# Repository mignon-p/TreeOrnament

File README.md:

This repository contains the [KiCad][1] and [Gerber][2] files for a
PCB Christmas ornament shaped like a Christmas tree.

The little tree has candy canes on the silkscreen, ornaments made out
of exposed copper, and a trunk made out of exposed FR4.  The garland
is made out of resistors, and the lights are LEDs, powered by a micro
USB connector on the back.

You can hang the ornament on your tree by putting a string through the
hole at the top of the ornament.  Or, you can use it as a standalone
decoration, in which case the USB cable in the back acts as a sort of
"[kickstand](kickstand.jpg)" to hold the tree up.

This README should contain enough information to build the ornament.
However, if you want more detailed, step-by-step instructions with
pictures, I've also written
[an Instructable on how to build the ornament][17].

## Bill of Materials

* USB Micro B connector, qty 1.  Würth part number 614105150721.
  Digi-Key part number [732-5958-1-ND][3].

* 1/8 watt resistors, qty 14.  Make sure the length of the resistor is
  around 3.3-3.6 mm.  The minimum resistor value you should use is 150
  Ohms.  However, I found that to be too bright, so I eventually
  settled on 1k Ohm resistors.  Especially if you use different LEDs
  than I did, you should experiment to see what resistor value gives
  you a brightness that you like.  For 1k Ohm resistors: Stackpole
  part number CF18JT1K00.  Digi-Key part number [CF18JT1K00CT-ND][4].

* 3mm LEDs, qty 14.  Just about any 3mm LED should do, but I used
  color-changing LEDs to [add a bit of motion][13] to the ornament.
  When soldering the LEDs, make sure the short leg of the LED goes
  into the square pad, and the long leg of the LED goes into the round
  pad.  For color-changing LEDs: SparkFun part number [COM-11448][5].
  Digi-Key part number [1568-1196-ND][6].

* Optional: 3.3µF 0805 ceramic capacitor, qty 3.  These probably
  aren't essential, but since decoupling capacitors are considered to
  be a good idea, I added pads for three capacitors on the back of the
  board.  (Though if you're using ordinary LEDs, you really don't need
  them, since the current will be constant.  I only added them because
  I'm using color-change LEDs, which probably use PWM to fade through
  the colors.)  Unlike all the other components, these are
  surface-mount, so they're a little trickier to solder.  It helps if
  you have a second person to hold the capacitor in place with
  tweezers, though it's [possible for one person to do it][22].
  Samsung part number CL21A335KPFNNNG.  Digi-Key part number
  [1276-6461-1-ND][7].

* Optional: string to hang the ornament.  Just about any string should
  do.  I used [Hemptique red cord][8].

And, of course, you'll also need a USB charger and Micro B USB cable
to power the ornament.

## Circuit board

Most fabs should work fine, although you'll probably want a fab that
offers green soldermask.  (That rules out OSH Park, unless you want
purple trees!)  I went with [EasyEDA][9] because they are inexpensive
and offer green soldermask.  (However, it appears that EasyEDA is
spinning off their circuit board manufacturing to the site
[JLCPCB][18].)

I went with a PCB thickness of 1.0mm, because that's what
[the datasheet for the USB connector][10] recommends.  (With a thicker
PCB, the pins of the USB connector won't protrude all the way through
the board.)  I chose the more expensive [ENIG][11] finish, because I
thought that would look better on the exposed-copper ornaments.

If you're not making any changes to the board, all you need to do is
zip up the files in the `gerber` directory, and upload the zipfile to
EasyEDA.  After uploading the zipfile, these are the options I chose
on the EasyEDA site:

Note that in the KiCad files and Gerber files, the "front" of the
board is actually the back, and vice-versa.  This is because EasyEDA
adds a customer ID number to the front of the board, but I wanted the
number to be on the actual back of the board, where it doesn't disrupt
the esthetics of the ornament.

I recommend ordering more boards than you need, because some of the
boards will have cosmetic defects.  (They still work fine
electrically, but just don't make an ornament that looks as nice.)  In
particular, the FR4 appears to have some red writing on it in places,
so every now and then that will show up in the trunk of a tree.

Another way to solve the problem of the red writing on the FR4 is to
paint the trunk.  (e. g. with flat brown [Testors enamel paint][16])

## License

This design is licensed under the
[Creative Commons Attribution-ShareAlike 4.0 International license][12].

Some of the footprints in `myLibrary.pretty` are based on footprints
in the [KiCad library][14], which is licensed under the
[KiCad library license][15] (which is now also CC-BY-SA-4.0, with an
exception).

## Other circuit board trees

I'm not the only one to have had this idea.  Here are some other folks
who have made tree-shaped Christmas ornaments out of circuit boards:

* [CyrilSneer][19]
* [platisd][20]
* [Circtistic][21]

However, I feel that my version has some advantages:

* More LEDs - My version has 14 LEDs.
* "Cleaner" front - Mine has all the circuit traces on the back, so
  the front is more esthetically pleasing.
* USB Powered - Mine uses a USB charger instead of a battery, so you
  can plug it in with the rest of the lights on your tree.

[1]: http://kicad.org/
[2]: https://en.wikipedia.org/wiki/Gerber_format
[3]: https://www.digikey.com/products/en?keywords=732-5958-1-ND
[4]: https://www.digikey.com/products/en?keywords=CF18JT1K00CT-ND
[5]: https://www.sparkfun.com/products/11448
[6]: https://www.digikey.com/products/en?keywords=1568-1196-ND
[7]: https://www.digikey.com/products/en?keywords=1276-6461-1-ND
[8]: https://smile.amazon.com/gp/product/B007IT72JS/
[9]: https://easyeda.com/order
[10]: http://katalog.we-online.de/em/datasheet/614105150721.pdf
[11]: https://en.wikipedia.org/wiki/Electroless_nickel_immersion_gold
[12]: https://creativecommons.org/licenses/by-sa/4.0/
[13]: https://youtu.be/PZnlEJhb-sY
[14]: https://github.com/KiCad/kicad-footprints
[15]: https://forum.kicad.info/t/kicad-library-licensing/7856
[16]: https://www.testors.com/product-catalog/testors-brands/testors/enamel-paint/enamel-paints
[17]: http://www.instructables.com/id/LED-Circuit-Board-Christmas-Tree-Ornament/
[18]: https://jlcpcb.com/quote
[19]: https://forum.kicad.info/t/christmas-ornaments-designed-with-kicad/8674/2
[20]: https://www.hackster.io/platisd/a-christmas-tree-pcb-ornament-8bc03b
[21]: http://circtistic.com/
[22]: https://youtu.be/cBgmY16goX0

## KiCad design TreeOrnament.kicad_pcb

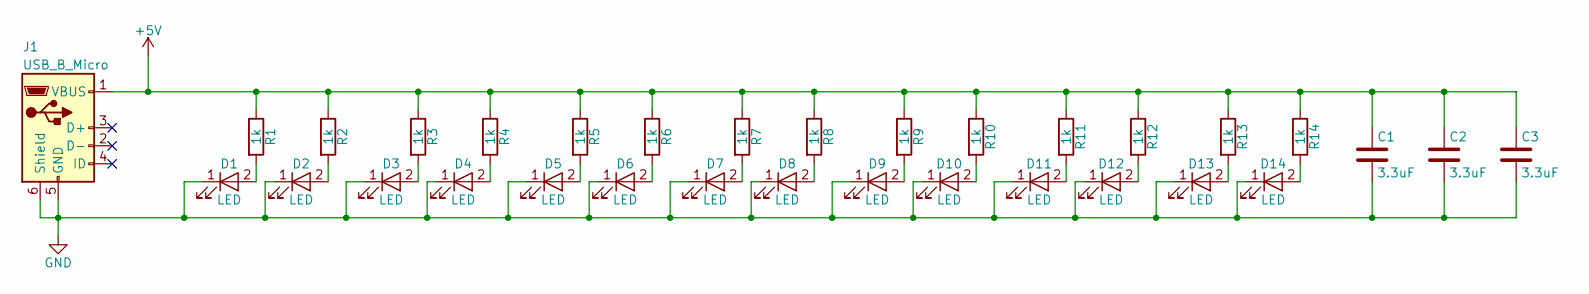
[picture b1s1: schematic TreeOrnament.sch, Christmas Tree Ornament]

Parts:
C1, C2, C3: 3.3uF; C_0805_HandSoldering
D1, D2, D3, D4, D5, D6, D7, D8, D9, D10, D11, D12, D13, D14: LED; LED_D3.0mm
J1: USB_B_Micro; USB_Micro-B_Wuerth-614105150721_Vertical_CircularHoles
R1, R2, R3, R4, R5, R6, R7, R8, R9, R10, R11, R12, R13, R14: 1k; R_Axial_DIN0204_L3.6mm_D1.6mm_P5.08mm_Horizontal

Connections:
+5V: C1.1, C2.1, C3.1, J1.1 (VBUS), R1.1, R2.1, R3.1, R4.1, R5.1, R6.1, R7.1, R8.1, R9.1, R10.1, R11.1, R12.1, R13.1, R14.1
GND: C1.2, C2.2, C3.2, D1.1 (K), D2.1 (K), D3.1 (K), D4.1 (K), D5.1 (K), D6.1 (K), D7.1 (K), D8.1 (K), D9.1 (K), D10.1 (K), D11.1 (K), D12.1 (K), D13.1 (K), D14.1 (K), J1.5 (GND), J1.6 (Shield)
unnamed: D1.2 (A), R1.2
unnamed: D2.2 (A), R2.2
unnamed: D3.2 (A), R3.2
unnamed: D4.2 (A), R4.2
unnamed: D5.2 (A), R5.2
unnamed: D6.2 (A), R6.2
unnamed: D7.2 (A), R7.2
unnamed: D8.2 (A), R8.2
unnamed: D9.2 (A), R9.2
unnamed: D10.2 (A), R10.2
unnamed: D11.2 (A), R11.2
unnamed: D12.2 (A), R12.2
unnamed: D13.2 (A), R13.2
unnamed: D14.2 (A), R14.2

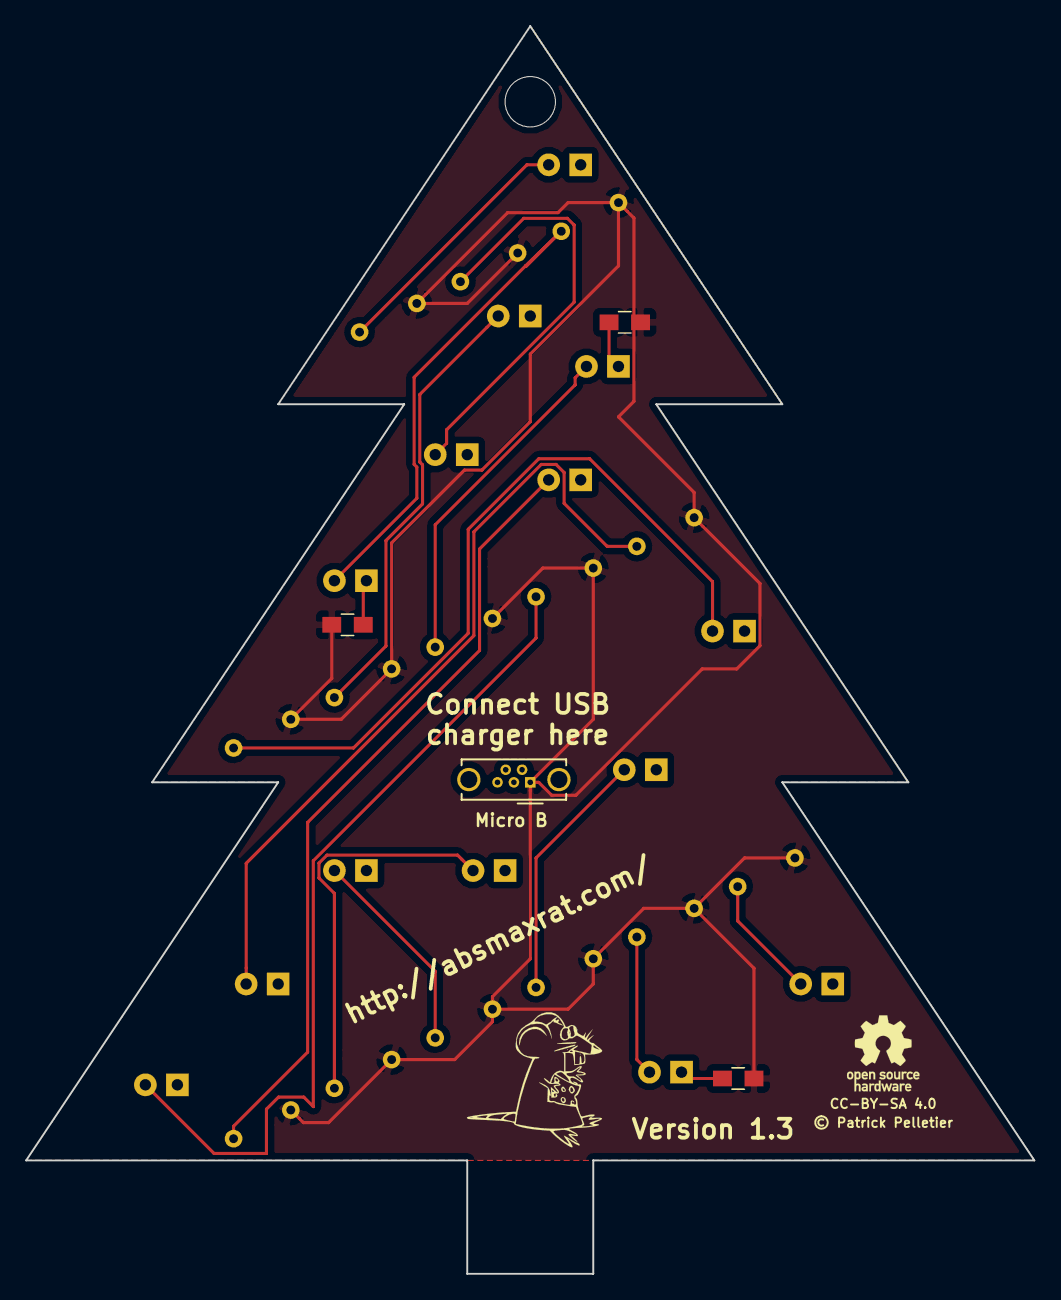
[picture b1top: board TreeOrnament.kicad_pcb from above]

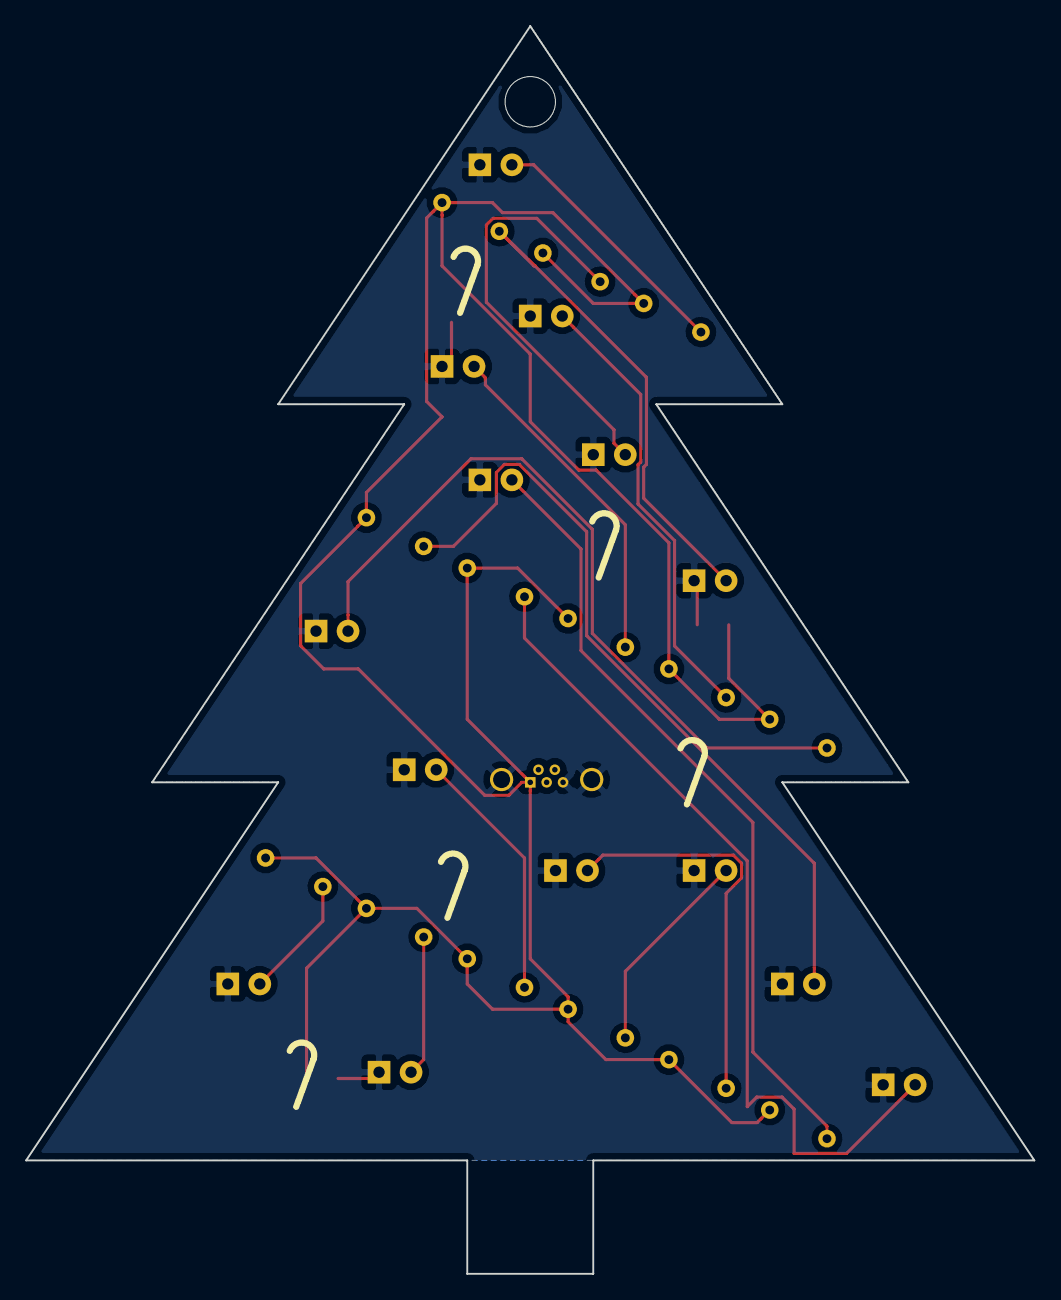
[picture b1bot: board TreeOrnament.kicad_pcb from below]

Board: 2 copper layers, 80.0 x 99.0 mm, 32 parts (28 on the bottom side), 16 nets.

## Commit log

2017-10-25 Add myLibrary
2017-10-25 Add some LEDs.
2017-10-25 Associate footprints.
2017-10-25 import netlist into PCB
2017-10-25 xmas tree outline
2017-10-25 draw the tree
2017-10-25 change angle of resistors
2017-10-25 add more LEDs to schematic
2017-10-25 place LEDs on tree
2017-10-25 remove extra resistor and LEDs
2017-10-25 Footprints for candy cane and ornament.
2017-10-25 Add candy canes and ornaments to tree.
2017-10-25 expose bare FR4 for tree trunk
2017-10-25 Adjust garlands.
2017-10-25 Footprints without silk.
2017-10-25 use silkless footprints
2017-10-25 update footprints
2017-10-25 add Hole footprint
2017-10-25 Put hole at top of ornament to hang it.
2017-10-25 wire up the tree
2017-10-25 fill zones.
2017-10-25 Add text on back silkscreen.
2017-10-25 Remove last bit of silkscreen on the LEDs.
2017-10-26 Reduce height to 99mm to fix in a 100x100mm box.
2017-10-26 settings for Gerber export
2017-10-28 Add Gerbers.
2017-10-28 wire up LEDs in parallel
2017-10-28 Use smaller resistor footprint, e. g. for Stackpole CF18JT150R.
2017-10-28 place new resistors
2017-10-28 remove year from silkscreen
2017-10-28 wire LEDs to resistors
2017-10-28 finish wiring up the tree
2017-10-28 Use 150 Ohm resistors.
2017-10-28 Propagate 150 Ohms to PCB, not that it really matters.
2017-10-28 Have ornament just expose copper underneath, but not be a copper pad.
2017-10-28 Have trunk expose board on both sides.
2017-10-28 Use newer version of Micro B footprint.
2017-10-28 Generate new gerbers.
2017-10-31 Flip the board over.
    (This way the customer ID will be on the "back" instead of the "front".)
2017-10-31 Change signature text to include the year again.
2017-11-03 Add some optional SMT decoupling caps.
2017-11-03 Regenerated Gerbers.
2017-11-04 label USB port as being Micro B
2017-11-04 Regenerate Gerbers.
2017-11-19 Remove unused symbols from library.
2017-11-20 Add README.
2017-11-25 Change resistor value from 150 to 1k.
2017-11-25 Add github URL and KiCad logo.
2017-11-26 Add link to video.
2017-11-26 Licensing info for footprints.
2017-11-27 Mention the issue of cosmetic defects.
2017-12-01 Suggest painting the trunk.
2017-12-15 Use photo of ornament on tree.
2017-12-17 Add CC-BY-SA to silkscreen.
2018-01-03 Mention Instructable and JLCPCB.
2018-01-06 Mention other circuit board trees.
2018-01-06 Link to a better video of the ornament.
2018-01-06 One person can solder capacitors; link to video.
2018-09-23 Add AbsMaxRat logo and URL to silkscreen.
2021-10-22 Link to kicad.org
    https://forum.kicad.info/t/warning-avoid-all-links-to-kicad-pcb-org-use-kicad-org/31521

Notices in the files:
TreeOrnament.kicad_pcb:
© Patrick Pelletier
